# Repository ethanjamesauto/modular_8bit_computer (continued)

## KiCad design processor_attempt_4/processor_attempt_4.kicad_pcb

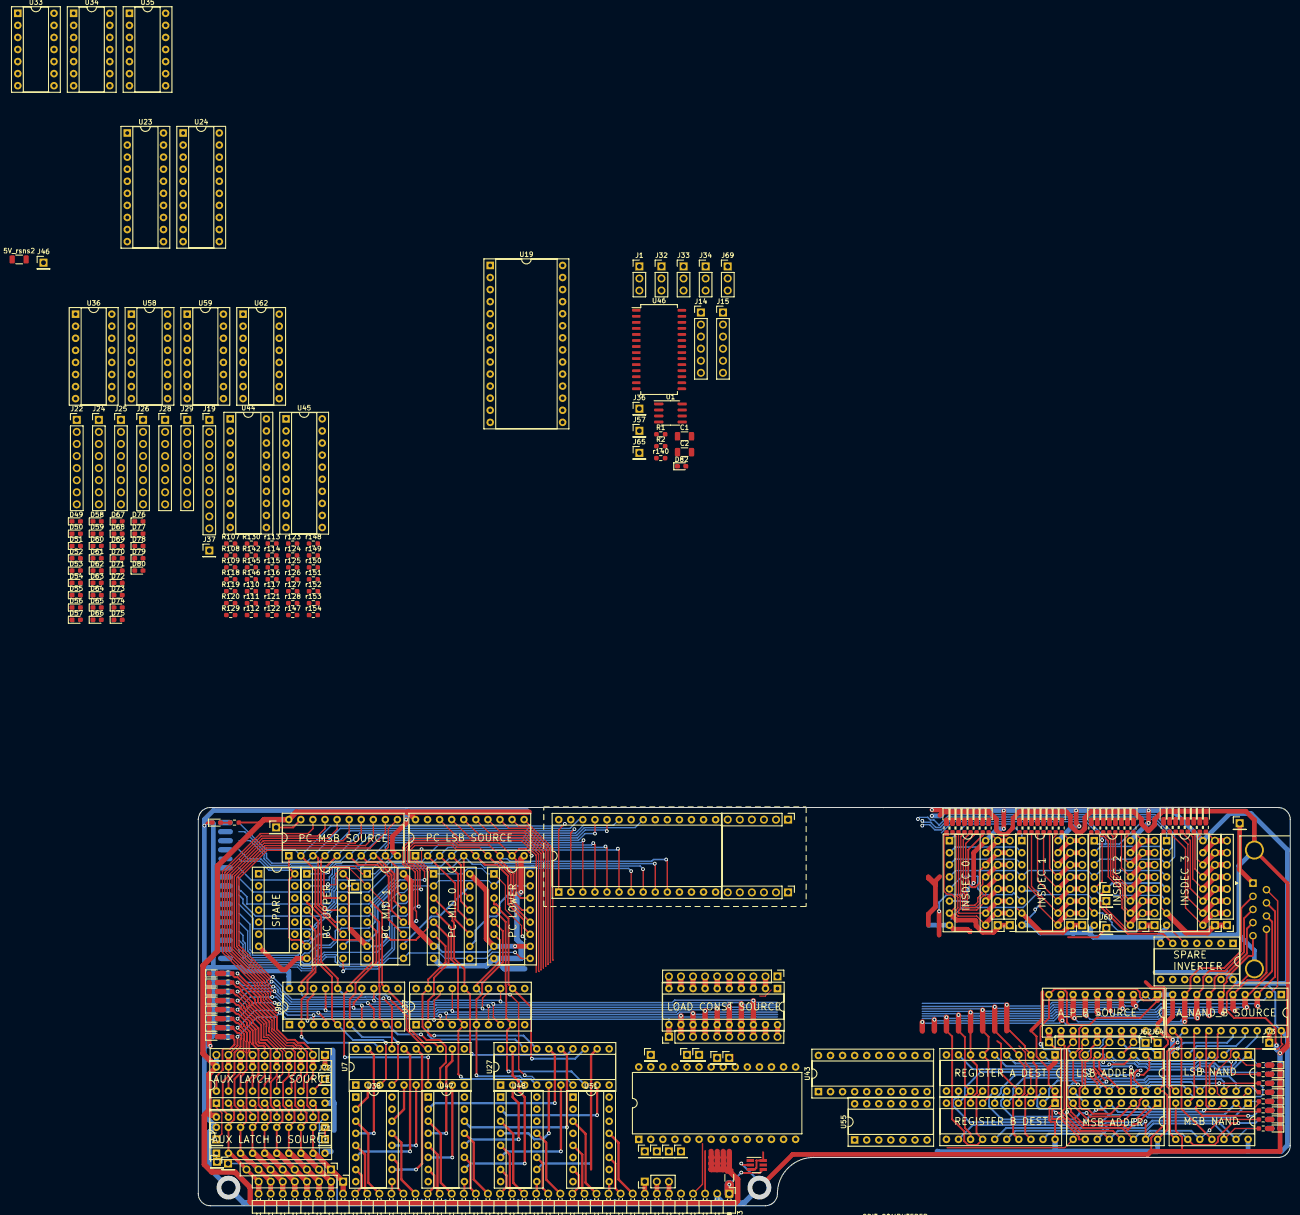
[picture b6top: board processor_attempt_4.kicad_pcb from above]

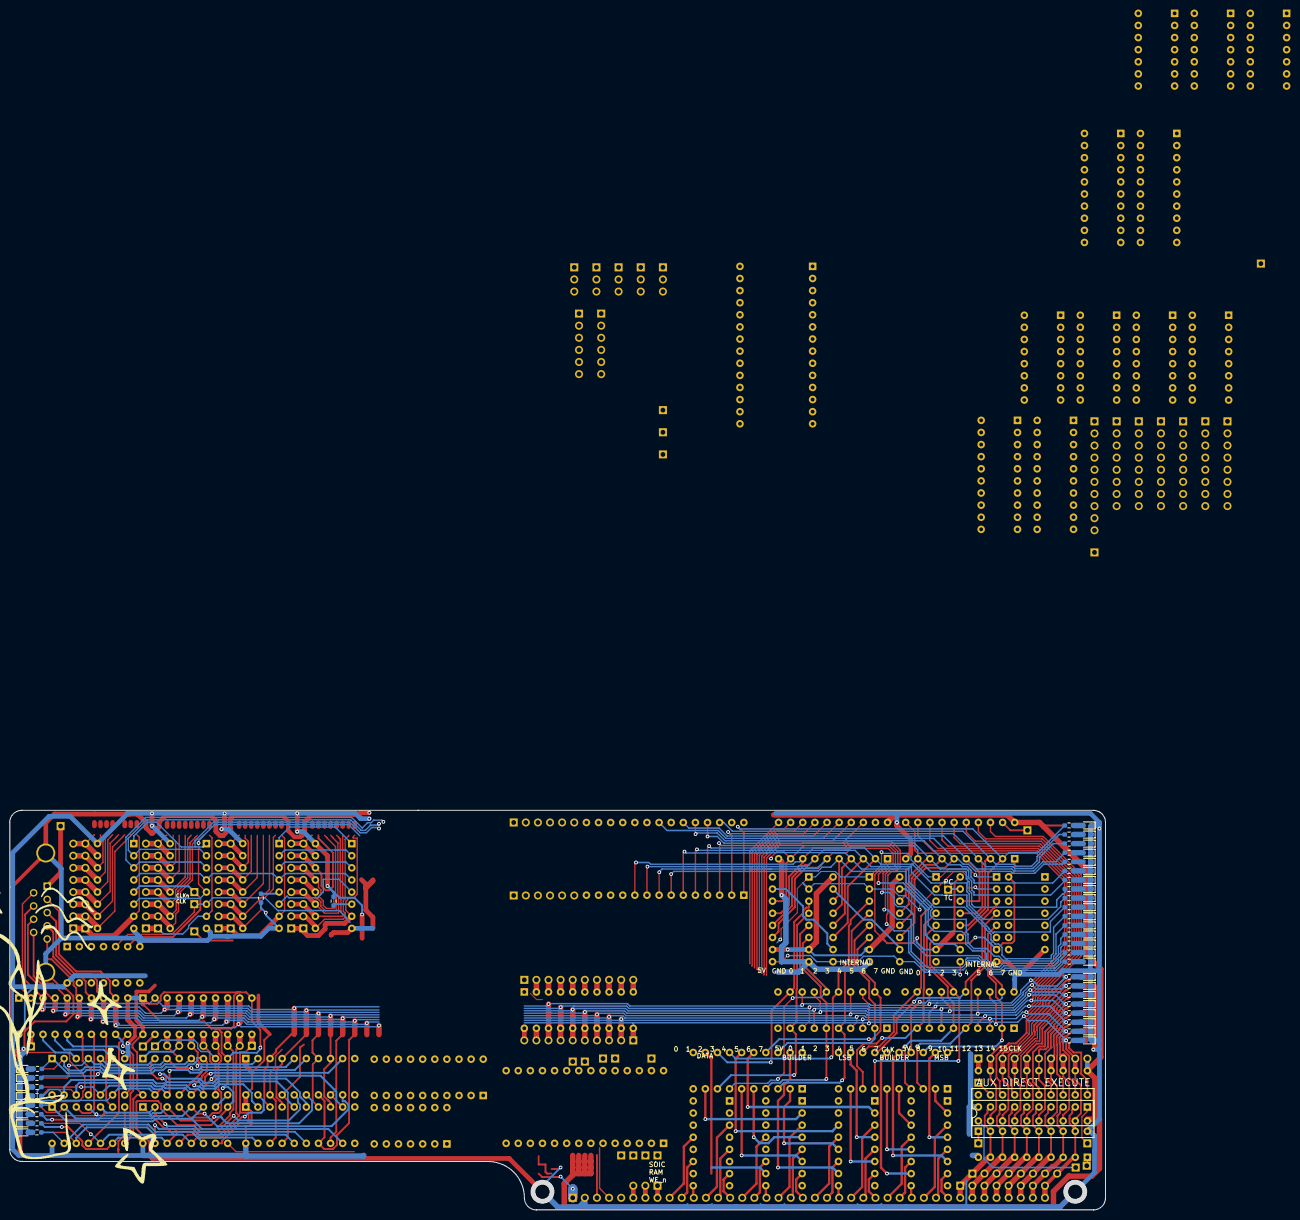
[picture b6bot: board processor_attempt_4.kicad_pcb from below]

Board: 2 copper layers, 229.9 x 83.8 mm, 351 parts (67 on the bottom side), 389 nets.

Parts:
5V_rsns1: 1; R_1206_3216Metric
5V_rsns2: 10k; R_1206_3216Metric
C1, C2: C; C_1206_3216Metric
D1, D17, D25, D33, D41, D49, D49#2, D50, D50#2, D51, D51#2, D52, D52#2, D53, D53#2, D54, D54#2, D55, D55#2, D56, D56#2, D57, D57#2, D58, D58#2, D59, D59#2, D60, D60#2, D61, D61#2, D62, D62#2, D63, D63#2, D64, D64#2, D65, D65#2, D66, D66#2, D67, D67#2, D68, D68#2, D69, D69#2, D70, D70#2, D71, D71#2, D72, D72#2, D73, D73#2, D74, D74#2, D75, D75#2, D76, D76#2, D77, D77#2, D78, D78#2, D79, D79#2, D80, D80#2: A0; LED_0603_1608Metric_Pad1.05x0.95mm_HandSolder
D2, D18, D26, D34, D42: A1; LED_0603_1608Metric_Pad1.05x0.95mm_HandSolder
D3, D19, D27, D35, D43: A2; LED_0603_1608Metric_Pad1.05x0.95mm_HandSolder
D4, D20, D28, D36, D44: A3; LED_0603_1608Metric_Pad1.05x0.95mm_HandSolder
D5, D21, D29, D37, D45, D82: A4; LED_0603_1608Metric_Pad1.05x0.95mm_HandSolder
D6, D22, D30, D38, D46: A5; LED_0603_1608Metric_Pad1.05x0.95mm_HandSolder
D7, D23, D31, D39, D47: A6; LED_0603_1608Metric_Pad1.05x0.95mm_HandSolder
D8, D24, D32, D40, D48: A7; LED_0603_1608Metric_Pad1.05x0.95mm_HandSolder
D9: A8; LED_0603_1608Metric_Pad1.05x0.95mm_HandSolder
D10: A9; LED_0603_1608Metric_Pad1.05x0.95mm_HandSolder
D11: A10; LED_0603_1608Metric_Pad1.05x0.95mm_HandSolder
D12: A11; LED_0603_1608Metric_Pad1.05x0.95mm_HandSolder
D13: A12; LED_0603_1608Metric_Pad1.05x0.95mm_HandSolder
D14: A13; LED_0603_1608Metric_Pad1.05x0.95mm_HandSolder
D15: A14; LED_0603_1608Metric_Pad1.05x0.95mm_HandSolder
D16: A15; LED_0603_1608Metric_Pad1.05x0.95mm_HandSolder
D81: 5V_RAW; LED_0603_1608Metric_Pad1.05x0.95mm_HandSolder
J1, J31, J32, J33, J34, J69: Conn_01x03_Pin; PinHeader_1x03_P2.54mm_Vertical
J3: Conn_01x40_Pin; PinHeader_1x40_P2.54mm_Horizontal
J4, J4#2, J20, J22, J22#2, J23, J24, J24#2, J25, J25#2, J26, J26#2, J27, J28, J28#2, J29, J29#2: Conn_01x08_Pin; PinHeader_1x08_P2.54mm_Vertical
J8, J18, J19, J19#2: Conn_01x10_Pin; PinHeader_1x10_P2.54mm_Vertical
J14, J15, J16, J17: Conn_01x06_Pin; PinHeader_1x06_P2.54mm_Vertical
J21: DB9_Female_MountingHoles; DSUB-9_Female_Horizontal_P2.77x2.84mm_EdgePinOffset4.94mm_H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
J30, J35, J40, J42: Conn_01x01_Pin; PinHeader_1x01_P2.54mm_Vertical
J36, J37, J41, J43, J44, J46, J47, J48, J49, J50, J51, J52, J57, J60, J62, J64, J65, J67, J70, J71, J72, J73, J74: J; PinHeader_1x01_P2.54mm_Vertical
J39: Clock_Aux_Latch_0; PinHeader_1x01_P2.54mm_Vertical
R1, R2, R142#2: R; R_0603_1608Metric_Pad0.98x0.95mm_HandSolder
R107, R108, R109, R118, R119, R120, R129, R130, R141, R142, R145, R146: 0; R_0603_1608Metric_Pad0.98x0.95mm_HandSolder
U1: NE555D; SOIC-8_3.9x4.9mm_P1.27mm
U2, U3, U4, U5: 74LS161; DIP-16_W7.62mm_Socket
U6, U7, U24, U27, U37, U40, U41, U44, U45: 74LS273; DIP-20_W7.62mm_Socket
U18, U19: 28C256; DIP-28_W15.24mm_Socket
U21, U23, U29, U30, U31, U49, U50: 74LS245; DIP-20_W7.62mm_Socket
U25, U26: 74LS574; DIP-20_W7.62mm_Socket
U28: HM62256BLP; DIP-28_W15.24mm
U32, U39: 74LS283; DIP-16_W7.62mm_Socket
U33, U34: 74LS32; DIP-14_W7.62mm_Socket
U35, U55: 74LS30; DIP-14_W7.62mm_Socket
U36, U57, U58, U58#2, U59, U59#2, U60: 74LS138; DIP-16_W7.62mm_Socket
U38, U47, U48, U51: 74LS367; DIP-16_W7.62mm_Socket
U42, U56: 74LS04; DIP-14_W7.62mm_Socket
U43: 74HC688; DIP-20_W7.62mm_Socket
U46: HM62256BLP; SOIC-28W_7.5x18.7mm_P1.27mm
U52, U53: 74LS00; DIP-14_W7.62mm_Socket
U61: 74LVC1G08; SOT-23-6_Handsoldering
U62: DIP-16_W7.62mm_Socket
r51, r52, r53, r54, r55, r56, r57, r58, r59, r60, r61, r62, r63, r64, r65, r66, r67, r68, r69, r70, r71, r72, r73, r74, r75, r76, r77, r78, r79, r80, r81, r82, r83, r84, r85, r86, r87, r88, r89, r90, r91, r92, r93, r94, r95, r96, r97, r98, r107, r108, r109, r110, r110#2, r111, r111#2, r112, r112#2, r113, r113#2, r114, r114#2, r115, r115#2, r116, r116#2, r117, r117#2, r118, r119, r120, r121, r121#2, r122, r122#2, r123, r123#2, r124, r124#2, r125, r125#2, r126, r126#2, r127, r127#2, r128, r128#2, r129, r130, r131, r132, r133, r134, r135, r136, r137, r138, r139, r140, r147, r148, r149, r150, r151, r152, r153, r154: 470; R_0603_1608Metric_Pad0.98x0.95mm_HandSolder

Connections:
+5V: 5V_rsns1.2, 5V_rsns2.2, J3.1, J8.10, J18.1, J19.10, J19#2.10, R1.1, R118.1, R141.1, U1.4 (R), U1.8 (VCC), U2.7 (CEP), U2.10 (CET), U2.16 (VCC), U3.7 (CEP), U3.16 (VCC), U4.7 (CEP), U4.16 (VCC), U5.7 (CEP), U5.16 (VCC), U6.20 (VCC), U7.20 (VCC), U18.27 (~WE), U18.28 (VCC), U19.27 (~WE), U19.28 (VCC), U21.20 (VCC), U23.1 (A->B), U23.20 (VCC), U24.20 (VCC), U25.20 (VCC), U26.20 (VCC), U27.20 (VCC), U28.28 (VCC), U29.1 (A->B), U29.20 (VCC), U30.1 (A->B), U30.20 (VCC), U31.1 (A->B), U31.20 (VCC), U32.16 (VCC), U33.14 (VCC), U34.14 (VCC), U35.14 (VCC), U36.16 (VCC), U37.20 (VCC), U38.16 (VCC), U39.16 (VCC), U40.1 (~Mr), U40.20 (VCC), U41.1 (~Mr), U41.20 (VCC), U42.14 (VCC), U43.20 (VCC), U44.1 (~Mr), U44.20 (VCC), U45.1 (~Mr), U45.20 (VCC), U46.28 (VCC), U47.16 (VCC), U48.16 (VCC), U49.20 (VCC), U50.20 (VCC), U51.16 (VCC), U52.14 (VCC), U53.14 (VCC), U55.14 (VCC), U56.14 (VCC), U57.16 (VCC), U58.16 (VCC), U58#2.16 (VCC), U59.16 (VCC), U59#2.16 (VCC), U60.16 (VCC), U61.5 (VCC), r139.2
/5V_raw: 5V_rsns1.1, U61.4
/APB_0: J20.8, U32.4 (S1), U49.18 (B0)
/APB_1: J20.7, U32.1 (S2), U49.17 (B1)
/APB_2: J20.6, U32.13 (S3), U49.16 (B2)
/APB_3: J20.5, U32.10 (S4), U49.15 (B3)
/APB_4: J20.4, U39.4 (S1), U49.14 (B4)
/APB_5: J20.3, U39.1 (S2), U49.13 (B5)
/APB_6: J20.2, U39.13 (S3), U49.12 (B6)
/APB_7: J20.1, U39.10 (S4), U49.11 (B7)
/A_nand_B_0: U50.18 (B0), U52.3
/A_nand_B_1: U50.17 (B1), U52.6
/A_nand_B_2: U50.16 (B2), U52.8
/A_nand_B_3: U50.15 (B3), U52.11
/A_nand_B_4: U50.14 (B4), U53.3
/A_nand_B_5: U50.13 (B5), U53.6
/A_nand_B_6: U50.12 (B6), U53.8
/A_nand_B_7: U50.11 (B7), U53.11
/Aux_Bus_0_LSB: J3.33, J4.1, U21.2 (A0), U25.9 (D7), U26.9 (D7)
/Aux_Bus_1: J3.34, J4.2, U21.3 (A1), U25.8 (D6), U26.8 (D6)
/Aux_Bus_2: J3.35, J4.3, U21.4 (A2), U25.7 (D5), U26.7 (D5)
/Aux_Bus_3: J3.36, J4.4, U21.5 (A3), U25.6 (D4), U26.6 (D4)
/Aux_Bus_4: J3.37, J4.5, U21.6 (A4), U25.5 (D3), U26.5 (D3)
/Aux_Bus_5: J3.38, J4.6, U21.7 (A5), U25.4 (D2), U26.4 (D2)
/Aux_Bus_6: J3.39, J4.7, J4#2.7, U21.8 (A6), U25.3 (D1), U26.3 (D1)
/Aux_Bus_7_MSB: J3.40, J4.8, U21.9 (A7), U25.2 (D0), U26.2 (D0)
/CLOCK_to_pc: J1.2, J32.1, J32.2, J32.3, J33.1, J33.2, J33.3, J34.1, J34.2, J34.3, J67.1, U2.2 (CP), U3.2 (CP), U4.2 (CP), U5.2 (CP), U42.5, U59.6 (E3), r140.2
/CLOCK_to_pc_n: J70.1, U42.6, U60.5 (E2)
/Data_Bus_0_LSB: J3.9, U51.13 (O6b)
/Data_Bus_1: J3.10, U51.11 (O5b)
/Data_Bus_2: J3.11, U51.9 (O4a)
/Data_Bus_3: J3.12, U51.3 (O1a)
/Data_Bus_4: J3.13, U51.5 (O2a)
/Data_Bus_5: J3.14, U51.7 (O3a)
/Data_Bus_6: J3.15, U48.13 (O6b)
/Data_Bus_7_MSB: J3.16, U48.11 (O5b)
/INTERNAL_BUS_0: J8.2, J19.8, J21.6, U6.13 (D4), U25.12 (Q7), U26.12 (Q7), U28.11 (Q0), U29.11 (B7), U30.11 (B7), U31.18 (B0), U37.13 (D4), U40.3 (D0), U41.3 (D0), U44.3 (D0), U45.3 (D0), U46.11 (Q0), U49.2 (A0), U50.2 (A0), r67.2
/INTERNAL_BUS_1: J8.3, J19.7, J21.7, U6.8 (D3), U25.13 (Q6), U26.13 (Q6), U28.12 (Q1), U29.12 (B6), U30.12 (B6), U31.17 (B1), U37.8 (D3), U40.4 (D1), U41.4 (D1), U44.4 (D1), U45.4 (D1), U46.12 (Q1), U49.3 (A1), U50.3 (A1), r68.2
/INTERNAL_BUS_2: J8.4, J19.6, J21.8, U6.7 (D2), U25.14 (Q5), U26.14 (Q5), U28.13 (Q2), U29.13 (B5), U30.13 (B5), U31.16 (B2), U37.7 (D2), U40.7 (D2), U41.7 (D2), U44.7 (D2), U45.7 (D2), U46.13 (Q2), U49.4 (A2), U50.4 (A2), r69.2
/INTERNAL_BUS_3: J8.5, J19.5, J21.9, U6.14 (D5), U25.15 (Q4), U26.15 (Q4), U28.15 (Q3), U29.14 (B4), U30.14 (B4), U31.15 (B3), U37.14 (D5), U40.8 (D3), U41.8 (D3), U44.8 (D3), U45.8 (D3), U46.15 (Q3), U49.5 (A3), U50.5 (A3), r70.2
/INTERNAL_BUS_4: J8.6, J19.4, J21.5, U6.17 (D6), U25.16 (Q3), U26.16 (Q3), U28.16 (Q4), U29.15 (B3), U30.15 (B3), U31.14 (B4), U37.17 (D6), U40.13 (D4), U41.13 (D4), U44.13 (D4), U45.13 (D4), U46.16 (Q4), U49.6 (A4), U50.6 (A4), r71.2
/INTERNAL_BUS_5: J8.7, J19.3, J21.4, U6.4 (D1), U25.17 (Q2), U26.17 (Q2), U28.17 (Q5), U29.16 (B2), U30.16 (B2), U31.13 (B5), U37.4 (D1), U40.14 (D5), U41.14 (D5), U44.14 (D5), U45.14 (D5), U46.17 (Q5), U49.7 (A5), U50.7 (A5), r72.2
/INTERNAL_BUS_6: J8.8, J19.2, J21.3, U6.3 (D0), U25.18 (Q1), U26.18 (Q1), U28.18 (Q6), U29.17 (B1), U30.17 (B1), U31.12 (B6), U37.3 (D0), U40.17 (D6), U41.17 (D6), U44.17 (D6), U45.17 (D6), U46.18 (Q6), U49.8 (A6), U50.8 (A6), r73.2
/INTERNAL_BUS_7: J8.9, J19.1, J21.2, U6.18 (D7), U25.19 (Q0), U26.19 (Q0), U28.19 (Q7), U29.18 (B0), U30.18 (B0), U31.11 (B7), U37.18 (D7), U40.18 (D7), U41.18 (D7), U44.18 (D7), U45.18 (D7), U46.19 (Q7), U49.9 (A7), U50.9 (A7), r74.2
/Load_Constant_OE_n: J19.9, J19#2.9, U31.19 (CE)
/PC_0: J69.1, J69.2, J69.3, U2.14 (Q0), U30.9 (A7), r51.2
/PC_1: U2.13 (Q1), U18.10 (A0), U19.10 (A0), U30.8 (A6), r52.2
/PC_2: U2.12 (Q2), U18.9 (A1), U19.9 (A1), U30.7 (A5), r53.2
/PC_3: U2.11 (Q3), U18.8 (A2), U19.8 (A2), U30.6 (A4), r54.2
/PC_4: U3.14 (Q0), U18.7 (A3), U19.7 (A3), U30.5 (A3), r55.2
/PC_5: U3.13 (Q1), U18.6 (A4), U19.6 (A4), U30.4 (A2), r56.2
/PC_6: U3.12 (Q2), U18.5 (A5), U19.5 (A5), U30.3 (A1), r57.2
/PC_7: U3.11 (Q3), U18.4 (A6), U19.4 (A6), U30.2 (A0), r58.2
/PC_8: U4.14 (Q0), U18.3 (A7), U19.3 (A7), U29.9 (A7), r59.2
/PC_9: U4.13 (Q1), U18.25 (A8), U19.25 (A8), U29.8 (A6), r60.2
/PC_10: U4.12 (Q2), U18.24 (A9), U19.24 (A9), U29.7 (A5), r61.2
/PC_11: U4.11 (Q3), U18.21 (A10), U19.21 (A10), U29.6 (A4), r62.2
/PC_12: U5.14 (Q0), U18.23 (A11), U19.23 (A11), U29.5 (A3), r63.2
/PC_13: U5.13 (Q1), U18.2 (A12), U19.2 (A12), U29.4 (A2), r64.2
/PC_14: U5.12 (Q2), U18.26 (A13), U19.26 (A13), U29.3 (A1), r65.2
/PC_15: U5.11 (Q3), U18.1 (A14), U19.1 (A14), U29.2 (A0), r66.2
/PC_load_n: U2.9 (~PE), U3.9 (~PE), U4.9 (~PE), U5.9 (~PE)
/RA_0: U32.5 (A1), U40.2 (Q0), U43.12 (R4), U52.2, r83.2
/RA_1: U32.3 (A2), U40.5 (Q1), U43.14 (R5), U52.4, r84.2
/RA_2: U32.14 (A3), U40.6 (Q2), U43.16 (R6), U52.10, r85.2
/RA_3: U32.12 (A4), U40.9 (Q3), U43.18 (R7), U52.12, r86.2
/RA_4: U39.5 (A1), U40.12 (Q4), U43.3 (R0), U53.2, r87.2
/RA_5: U39.3 (A2), U40.15 (Q5), U43.5 (R1), U53.4, r88.2
/RA_6: U39.14 (A3), U40.16 (Q6), U43.7 (R2), U53.10, r89.2
/RA_7: U39.12 (A4), U40.19 (Q7), U43.9 (R3), U53.12, r90.2
/RB_0: U32.6 (B1), U41.2 (Q0), U43.11 (P4), U52.1, U55.2, r91.2
/RB_1: U32.2 (B2), U41.5 (Q1), U43.13 (P5), U52.5, U55.1, r92.2
/RB_2: U32.15 (B3), U41.6 (Q2), U43.15 (P6), U52.9, U55.12, r93.2
/RB_3: U32.11 (B4), U41.9 (Q3), U43.17 (P7), U52.13, U55.11, r94.2
/RB_4: U39.6 (B1), U41.12 (Q4), U43.2 (P0), U53.1, U55.6, r95.2
/RB_5: U39.2 (B2), U41.15 (Q5), U43.4 (P1), U53.5, U55.5, r96.2
/RB_6: U39.15 (B3), U41.16 (Q6), U43.6 (P2), U53.9, U55.4, r97.2
/RB_7: U39.11 (B4), U41.19 (Q7), U43.8 (P3), U53.13, U55.3, r98.2
/a_equals_b: J37.1, U43.19 (P=R)
/a_plus_b_carry_out: U33.9, U39.9 (C4)
/addr_bus_0: J3.17, U48.9 (O4a)
/addr_bus_1: J3.18, U48.3 (O1a)
/addr_bus_2: J3.19, U48.5 (O2a)
/addr_bus_3: J3.20, U48.7 (O3a)
/addr_bus_4: J3.21, U47.13 (O6b)
/addr_bus_5: J3.22, U47.11 (O5b)
/addr_bus_6: J3.23, U47.9 (O4a)
/addr_bus_7: J3.24, U47.3 (O1a)
/addr_bus_8: J3.25, U47.5 (O2a)
/addr_bus_9: J3.26, U47.7 (O3a)
/addr_bus_10: J3.27, U38.13 (O6b)
/addr_bus_11: J3.28, U38.11 (O5b)
/addr_bus_12: J3.29, U38.9 (O4a)
/addr_bus_13: J3.30, U38.3 (O1a)
/addr_bus_14: J3.31, U38.5 (O2a)
/addr_bus_15: J3.32, U38.7 (O3a)
/addr_pre_buf_0: U27.12 (Q4), U48.10 (I4)
/addr_pre_buf_1: U27.9 (Q3), U48.2 (I1)
/addr_pre_buf_2: U27.5 (Q1), U48.4 (I2)
/addr_pre_buf_3: U27.6 (Q2), U48.6 (I3)
/addr_pre_buf_4: U27.15 (Q5), U47.14 (I6)
/addr_pre_buf_5: U27.2 (Q0), U47.12 (I5)
/addr_pre_buf_6: U27.19 (Q7), U47.10 (I4)
/addr_pre_buf_7: U27.16 (Q6), U47.2 (I1)
/addr_pre_buf_8: U7.12 (Q4), U47.4 (I2)
/addr_pre_buf_9: U7.9 (Q3), U47.6 (I3)
/addr_pre_buf_10: U7.5 (Q1), U38.14 (I6)
/addr_pre_buf_11: U7.6 (Q2), U38.12 (I5)
/addr_pre_buf_12: U7.15 (Q5), U38.10 (I4)
/addr_pre_buf_13: U7.2 (Q0), U38.2 (I1)
/addr_pre_buf_14: U7.19 (Q7), U38.4 (I2)
/addr_pre_buf_15: U7.16 (Q6), U38.6 (I3)
/b_equals_f_f: J57.1, U55.8
/clk: J1.1, J3.3, R108.1
/clock_build_constant: J22#2.1, J24#2.1, U36.7 (O7), r117#2.2
/clock_builder_lower: J22#2.8, J24#2.8, U36.15 (O0), r110.2
/clock_builder_upper: J22#2.7, J24#2.7, U36.14 (O1), r111.2
/clock_register_a: J22#2.5, J24#2.5, U36.12 (O3), r113.2
/clock_register_b: J22#2.4, J24#2.4, U36.11 (O4), r114.2
/cond_0: U33.3, U35.1
/cond_1: U33.6, U35.2
/cond_2: U33.8, U35.3
/cond_3: U33.11, U35.4
/cond_4: U34.3, U35.5
/cond_5: U34.6, U35.6
/cond_6: U34.8, U35.11
/cond_7: U34.11, U35.12
/ctrl_8: J22.8, J24.8, U58#2.15 (O0), r130.2
/ctrl_9: J22.7, J24.7, U58#2.14 (O1), r129.2
/ctrl_10: J22.6, J24.6, U58#2.13 (O2), r128.2
/ctrl_11: J22.5, J24.5, U58#2.12 (O3), r127.2
/ctrl_12: J22.4, J24.4, U58#2.11 (O4), r126.2
/ctrl_13: J22.3, J24.3, U58#2.10 (O5), r125#2.2
/ctrl_14: J22.2, J24.2, U58#2.9 (O6), r124#2.2
/ctrl_15: J22.1, J24.1, U58#2.7 (O7), r123.2
/ctrl_16: J26.8, J28#2.8, U59.15 (O0), r107.2
/ctrl_17: J26.7, J28#2.7, U59.14 (O1), r108.2
/ctrl_18: J26.6, J28#2.6, U59.13 (O2), r109.2
/ctrl_19: J26.5, J28#2.5, U59.12 (O3), r110#2.2
/ctrl_20: J26.4, J28#2.4, U59.11 (O4), r111#2.2
/ctrl_21: J26.3, J28#2.3, U59.10 (O5), r112#2.2
/ctrl_22: J26.2, J28#2.2, U59.9 (O6), r113#2.2
/ctrl_23: J26.1, J28#2.1, U59.7 (O7), r114#2.2
/ctrl_24: J25.8, J29.8, U60.15 (O0), r115.2
/ctrl_25: J25.7, J29.7, U60.14 (O1), r116#2.2
/ctrl_26: J25.6, J29.6, U60.13 (O2), r117.2
/ctrl_27: J25.5, J29.5, U60.12 (O3), r118.2
/ctrl_28: J25.4, J29.4, U60.11 (O4), r119.2
/ctrl_29: J25.3, J29.3, U60.10 (O5), r120.2
/ctrl_30: J25.2, J29.2, U60.9 (O6), r121.2
/ctrl_31: J25.1, J29.1, U60.7 (O7), r122.2
/external_write_enable_n: J22#2.2, J24#2.2, U36.9 (O6), r116.2
/extra_control_one: J23.3, J27.3, U34.5, U57.10 (O5), r133.2
/extra_control_three: J23.1, J27.1, U34.13, U57.7 (O7), r131.2
/extra_control_two: J23.2, J27.2, U34.10, U57.9 (O6), r132.2
/extra_control_zero: J23.4, J27.4, U7.11 (Cp), U27.11 (Cp), U34.2, U57.11 (O4), r134.2
/extra_dest_clock: J22#2.3, J24#2.3, U36.10 (O5), r115#2.2
/flag_0: J28.8, J29#2.8, U59#2.15 (O0), r147.2
/flag_1: J28.7, J29#2.7, U59#2.14 (O1), r148.2
/flag_2: J28.6, J29#2.6, U59#2.13 (O2), r149.2
/flag_3: J28.5, J29#2.5, U59#2.12 (O3), r150.2
/flag_4: J28.4, J29#2.4, U59#2.11 (O4), r151.2
/flag_5: J28.3, J29#2.3, U59#2.10 (O5), r152.2
/flag_6: J28.2, J29#2.2, U59#2.9 (O6), r153.2
/flag_7: J28.1, J29#2.1, U59#2.7 (O7), r154.2
/instruction_0: U18.11 (D0), U19.11 (D0), U21.18 (B0), U23.2 (A0), U24.3 (D0), r75.2
/instruction_1: U18.12 (D1), U19.12 (D1), U21.17 (B1), U23.3 (A1), U24.4 (D1), r76.2
/instruction_2: U18.13 (D2), U19.13 (D2), U21.16 (B2), U23.4 (A2), U24.7 (D2), r77.2
/instruction_3: R119.1, R145.1, U18.15 (D3), U19.15 (D3), U21.15 (B3), U23.5 (A3), U24.8 (D3), r78.2
/instruction_4: U18.16 (D4), U19.16 (D4), U21.14 (B4), U23.6 (A4), U24.13 (D4), r79.2
/instruction_5: U18.17 (D5), U19.17 (D5), U21.13 (B5), U23.7 (A5), U24.14 (D5), r80.2
/instruction_6: U18.18 (D6), U19.18 (D6), U21.12 (B6), U23.8 (A6), U24.17 (D6), r81.2
/instruction_7: R107.1, R120.1, R146.1, U18.19 (D7), U19.19 (D7), U21.11 (B7), U23.9 (A7), U24.18 (D7), r82.2
/instruction_valid_n: U58#2.4 (E1), U59.4 (E1), U60.4 (E1)
/jump_cond_a_equals_b: J23.8, J27.8, U33.2, U57.15 (O0), r138.2
/jump_cond_a_plus_b_carry_out: J23.6, J27.6, U33.10, U57.13 (O2), r136.2
/jump_cond_b_equals_f_f: J23.7, J27.7, U33.5, U57.14 (O1), r137.2
/jump_cond_b_negative: J23.5, J27.5, U33.13, U57.12 (O3), r135.2
/mar_0: U28.10 (A0), U45.2 (Q0), U46.10 (A0)
/mar_1: U28.9 (A1), U45.5 (Q1), U46.9 (A1)
/mar_2: U28.8 (A2), U45.6 (Q2), U46.8 (A2)
/mar_3: U28.7 (A3), U45.9 (Q3), U46.7 (A3)
/mar_4: U28.6 (A4), U45.12 (Q4), U46.6 (A4)
/mar_5: U28.5 (A5), U45.15 (Q5), U46.5 (A5)
/mar_6: U28.4 (A6), U45.16 (Q6), U46.4 (A6)
/mar_7: U28.3 (A7), U45.19 (Q7), U46.3 (A7)
/mar_8: U28.25 (A8), U44.2 (Q0), U46.25 (A8)
/mar_9: U28.24 (A9), U44.5 (Q1), U46.24 (A9)
/mar_10: U28.21 (A10), U44.6 (Q2), U46.21 (A10)
/mar_11: U28.23 (A11), U44.9 (Q3), U46.23 (A11)
/mar_12: U28.2 (A12), U44.12 (Q4), U46.2 (A12)
/mar_13: U28.26 (A13), U44.15 (Q5)
/mar_14: U28.1 (A14), U44.16 (Q6)
/pc_reset_n: 5V_rsns2.1, J3.4, U2.1 (~MR), U3.1 (~MR), U4.1 (~MR), U5.1 (~MR), U7.1 (~Mr), U24.1 (~Mr), U27.1 (~Mr)
/ram_write_enable_n: J22#2.6, J24#2.6, U36.13 (O2), r112.2
/source_0: J25#2.8, J26#2.8, U58.15 (O0), r121#2.2
/source_1: J25#2.7, J26#2.7, U58.14 (O1), r122#2.2
/source_2: J25#2.6, J26#2.6, U58.13 (O2), r123#2.2
/source_3: J25#2.5, J26#2.5, U58.12 (O3), r124.2
/source_4: J25#2.4, J26#2.4, U58.11 (O4), r125.2
/source_5: J25#2.3, J26#2.3, U58.10 (O5), r126#2.2
/source_6: J25#2.2, J26#2.2, U58.9 (O6), r127#2.2
/source_7: J25#2.1, J26#2.1, U58.7 (O7), r128#2.2
/to_PC_0: U2.3 (D0), U27.13 (D4), U37.12 (Q4)
/to_PC_1: U2.4 (D1), U27.8 (D3), U37.9 (Q3)
/to_PC_2: U2.5 (D2), U27.4 (D1), U37.6 (Q2)
/to_PC_3: U2.6 (D3), U27.7 (D2), U37.15 (Q5)
/to_PC_4: U3.3 (D0), U27.14 (D5), U37.16 (Q6)
/to_PC_5: U3.4 (D1), U27.3 (D0), U37.5 (Q1)
/to_PC_6: U3.5 (D2), U27.18 (D7), U37.2 (Q0)
/to_PC_7: U3.6 (D3), U27.17 (D6), U37.19 (Q7)
/to_PC_8: U4.3 (D0), U6.12 (Q4), U7.13 (D4)
/to_PC_9: U4.4 (D1), U6.9 (Q3), U7.8 (D3)
/to_PC_10: U4.5 (D2), U6.6 (Q2), U7.4 (D1)
/to_PC_11: U4.6 (D3), U6.15 (Q5), U7.7 (D2)
/to_PC_12: U5.3 (D0), U6.16 (Q6), U7.14 (D5)
/to_PC_13: U5.4 (D1), U6.5 (Q1), U7.3 (D0)
/to_PC_14: U5.5 (D2), U6.2 (Q0), U7.18 (D7)
/to_PC_15: U5.6 (D3), U6.19 (Q7), U7.17 (D6)
/to_insdec_0: U23.18 (B0), U58.1 (A0), U59#2.1 (A0)
/to_insdec_1: U23.17 (B1), U58.2 (A1), U59#2.2 (A1)
/to_insdec_2: U23.16 (B2), U58.3 (A2), U59#2.3 (A2)
/to_insdec_4: U23.14 (B4), U36.1 (A0), U57.1 (A0), U58#2.1 (A0)
/to_insdec_5: U23.13 (B5), U36.2 (A1), U57.2 (A1), U58#2.2 (A1)
/to_insdec_6: U23.12 (B6), U36.3 (A2), U57.3 (A2), U58#2.3 (A2)
/to_insdec_7: U23.11 (B7), U58#2.6 (E3)
/to_insdec_8: U24.2 (Q0), U59.1 (A0), U60.1 (A0)
/to_insdec_9: U24.5 (Q1), U59.2 (A1), U60.2 (A1)
/to_insdec_10: U24.6 (Q2), U59.3 (A2), U60.3 (A2)
/to_insdec_11: U24.9 (Q3), U59.5 (E2), U60.6 (E3)
GND: C1.2, C2.2, D1.1 (K), D2.1 (K), D3.1 (K), D4.1 (K), D5.1 (K), D6.1 (K), D7.1 (K), D8.1 (K), D9.1 (K), D10.1 (K), D11.1 (K), D12.1 (K), D13.1 (K), D14.1 (K), D15.1 (K), D16.1 (K), D17.1 (K), D18.1 (K), D19.1 (K), D20.1 (K), D21.1 (K), D22.1 (K), D23.1 (K), D24.1 (K), D25.1 (K), D26.1 (K), D27.1 (K), D28.1 (K), D29.1 (K), D30.1 (K), D31.1 (K), D32.1 (K), D33.1 (K), D34.1 (K), D35.1 (K), D36.1 (K), D37.1 (K), D38.1 (K), D39.1 (K), D40.1 (K), D41.1 (K), D42.1 (K), D43.1 (K), D44.1 (K), D45.1 (K), D46.1 (K), D47.1 (K), D48.1 (K), D49.1 (K), D49#2.2 (A), D50.2 (A), D50#2.1 (K), D51.1 (K), D51#2.2 (A), D52.2 (A), D52#2.1 (K), D53.1 (K), D53#2.2 (A), D54.1 (K), D54#2.2 (A), D55.1 (K), D55#2.2 (A), D56.2 (A), D56#2.1 (K), D57.1 (K), D57#2.2 (A), D58.1 (K), D58#2.2 (A), D59.1 (K), D59#2.2 (A), D60.2 (A), D60#2.1 (K), D61.2 (A), D61#2.1 (K), D62.2 (A), D62#2.1 (K), D63.2 (A), D63#2.1 (K), D64.2 (A), D64#2.1 (K), D65.1 (K), D65#2.2 (A), D66.1 (K), D66#2.2 (A), D67.1 (K), D67#2.2 (A), D68.2 (A), D68#2.1 (K), D69.1 (K), D69#2.2 (A), D70.1 (K), D70#2.2 (A), D71.1 (K), D71#2.2 (A), D72.2 (A), D72#2.1 (K), D73.2 (A), D73#2.1 (K), D74.2 (A), D74#2.1 (K), D75.1 (K), D75#2.2 (A), D76.2 (A), D76#2.1 (K), D77.2 (A), D77#2.1 (K), D78.2 (A), D78#2.1 (K), D79.1 (K), D79#2.2 (A), D80.1 (K), D80#2.2 (A), D81.1 (K), D82.1 (K), J3.2, J18.10, J21.0 (PAD), J60.1, R142#2.1, U1.1 (GND), U2.8 (GND), U3.8 (GND), U4.8 (GND), U5.8 (GND), U6.10 (GND), U7.10 (GND), U18.14 (GND), U18.20 (~CS), U18.22 (~OE), U19.14 (GND), U19.20 (~CS), U19.22 (~OE), U21.10 (GND), U23.10 (GND), U24.10 (GND), U25.10 (GND), U26.10 (GND), U27.10 (GND), U28.14 (GND), U29.10 (GND), U30.10 (GND), U31.10 (GND), U32.8 (GND), U33.7 (GND), U34.7 (GND), U35.7 (GND), U36.8 (GND), U37.10 (GND), U38.8 (GND), U39.8 (GND), U40.10 (GND), U41.10 (GND), U42.7 (GND), U43.1 (G), U43.10 (GND), U44.10 (GND), U45.10 (GND), U46.14 (GND), U47.8 (GND), U48.8 (GND), U49.1 (A->B), U49.10 (GND), U50.1 (A->B), U50.10 (GND), U51.8 (GND), U52.7 (GND), U53.7 (GND), U55.7 (GND), U56.7 (GND), U57.8 (GND), U58.8 (GND), U58#2.8 (GND), U59.8 (GND), U59#2.8 (GND), U60.8 (GND), U61.2, U62.8 (GND)
unnamed: D1.2 (A), r51.1
unnamed: D2.2 (A), r52.1
unnamed: D3.2 (A), r53.1
unnamed: D4.2 (A), r54.1
unnamed: D5.2 (A), r55.1
unnamed: D6.2 (A), r56.1
unnamed: D7.2 (A), r57.1
unnamed: D8.2 (A), r58.1
unnamed: D9.2 (A), r59.1
unnamed: D10.2 (A), r60.1
unnamed: D11.2 (A), r61.1
unnamed: D12.2 (A), r62.1
unnamed: D13.2 (A), r63.1
unnamed: D14.2 (A), r64.1
unnamed: D15.2 (A), r65.1
unnamed: D16.2 (A), r66.1
unnamed: D17.2 (A), r67.1
unnamed: D18.2 (A), r68.1
unnamed: D19.2 (A), r69.1
unnamed: D20.2 (A), r70.1
unnamed: D21.2 (A), r71.1
unnamed: D22.2 (A), r72.1
unnamed: D23.2 (A), r73.1
unnamed: D24.2 (A), r74.1
unnamed: D25.2 (A), r75.1
unnamed: D26.2 (A), r76.1
unnamed: D27.2 (A), r77.1
unnamed: D28.2 (A), r78.1
unnamed: D29.2 (A), r79.1
unnamed: D30.2 (A), r80.1
unnamed: D31.2 (A), r81.1
unnamed: D32.2 (A), r82.1
unnamed: D33.2 (A), r83.1
unnamed: D34.2 (A), r84.1
unnamed: D35.2 (A), r85.1
unnamed: D36.2 (A), r86.1
unnamed: D37.2 (A), r87.1
unnamed: D38.2 (A), r88.1
unnamed: D39.2 (A), r89.1
unnamed: D40.2 (A), r90.1
unnamed: D41.2 (A), r91.1
unnamed: D42.2 (A), r92.1
unnamed: D43.2 (A), r93.1
unnamed: D44.2 (A), r94.1
unnamed: D45.2 (A), r95.1
unnamed: D46.2 (A), r96.1
unnamed: D47.2 (A), r97.1
unnamed: D48.2 (A), r98.1
unnamed: D49.2 (A), r107.1
unnamed: D49#2.1 (K), r110.1
unnamed: D50#2.2 (A), r108.1
unnamed: D50.1 (K), r111.1
unnamed: D51.2 (A), r109.1
unnamed: D51#2.1 (K), r112.1
unnamed: D52#2.2 (A), r110#2.1
unnamed: D52.1 (K), r113.1
unnamed: D53.2 (A), r111#2.1
unnamed: D53#2.1 (K), r114.1
unnamed: D54.2 (A), r112#2.1
unnamed: D54#2.1 (K), r115#2.1
unnamed: D55.2 (A), r113#2.1
unnamed: D55#2.1 (K), r116.1
unnamed: D56#2.2 (A), r114#2.1
unnamed: D56.1 (K), r117#2.1
unnamed: D57.2 (A), r115.1
unnamed: D57#2.1 (K), r121#2.1
unnamed: D58.2 (A), r116#2.1
unnamed: D58#2.1 (K), r122#2.1
unnamed: D59.2 (A), r117.1
unnamed: D59#2.1 (K), r123#2.1
unnamed: D60#2.2 (A), r118.1
unnamed: D60.1 (K), r124.1
unnamed: D61#2.2 (A), r119.1
unnamed: D61.1 (K), r125.1
unnamed: D62#2.2 (A), r120.1
unnamed: D62.1 (K), r126#2.1
unnamed: D63#2.2 (A), r121.1
unnamed: D63.1 (K), r127#2.1
unnamed: D64#2.2 (A), r122.1
unnamed: D64.1 (K), r128#2.1
unnamed: D65.2 (A), r123.1
unnamed: D65#2.1 (K), r147.1
unnamed: D66.2 (A), r124#2.1
unnamed: D66#2.1 (K), r148.1
unnamed: D67.2 (A), r125#2.1
unnamed: D67#2.1 (K), r149.1
unnamed: D68#2.2 (A), r126.1
unnamed: D68.1 (K), r150.1
unnamed: D69.2 (A), r127.1
unnamed: D69#2.1 (K), r151.1
unnamed: D70.2 (A), r128.1
unnamed: D70#2.1 (K), r152.1
unnamed: D71.2 (A), r129.1
unnamed: D71#2.1 (K), r153.1
unnamed: D72#2.2 (A), r130.1
unnamed: D72.1 (K), r154.1
unnamed: D73.1 (K), r131.1
unnamed: D74.1 (K), r132.1
unnamed: D75#2.1 (K), r133.1
unnamed: D76.1 (K), r134.1
unnamed: D77.1 (K), r135.1
unnamed: D78.1 (K), r136.1
unnamed: D79#2.1 (K), r137.1
unnamed: D80#2.1 (K), r138.1
unnamed: D81.2 (A), r139.1
unnamed: D82.2 (A), r140.1
unnamed: J1.3, U1.3 (Q)
unnamed: J3.6, J31.3
unnamed: J3.7, J31.2
unnamed: J3.8, J31.1
unnamed: J8.1, U25.11 (Cp)
unnamed: J18.2, U31.2 (A0)
unnamed: J18.3, U31.3 (A1)
unnamed: J18.4, U31.4 (A2)
unnamed: J18.5, U31.5 (A3)
unnamed: J18.6, U31.6 (A4)
unnamed: J18.7, U31.7 (A5)
unnamed: J18.8, U31.8 (A6)
unnamed: J18.9, U31.9 (A7)
unnamed: J30.1, U26.1 (OE)
unnamed: J35.1, U25.1 (OE)
unnamed: J36.1, U23.19 (CE)
unnamed: J39.1, U26.11 (Cp)
unnamed: J40.1, U29.19 (CE)
unnamed: J42.1, U5.15 (TC)
unnamed: J46.1, U44.11 (Cp)
unnamed: J47.1, U28.20 (~CS)
unnamed: J48.1, U28.22 (~OE)
unnamed: J49.1, U28.27 (~WE)
unnamed: J50.1, U46.20 (~CS)
unnamed: J51.1, U46.22 (~OE)
unnamed: J52.1, U46.27 (~WE)
unnamed: J62.1, U32.7 (C0)
unnamed: J64.1, U49.19 (CE)
unnamed: J65.1, U24.11 (Cp)
unnamed: J71.1, U21.1 (A->B)
unnamed: J72.1, U21.19 (CE)
unnamed: J73.1, U50.19 (CE)
unnamed: J21.1, J74.1
unnamed: C1.1, U1.5 (CV)
unnamed: R1.2, R2.1, U1.7 (DIS)
unnamed: C2.1, R2.2, U1.2 (TR), U1.6 (THR)
unnamed: U2.15 (TC), U3.10 (CET)
unnamed: U3.15 (TC), U4.10 (CET)
unnamed: U4.15 (TC), U5.10 (CET)
unnamed: U32.9 (C4), U39.7 (C0)
unnamed: R109.2, U36.4 (E1)
unnamed: R108.2, U36.5 (E2)
unnamed: R107.2, U36.6 (E3)
unnamed: R146.2, U57.4 (E1)
unnamed: R145.2, U57.5 (E2)
unnamed: R141.2, U57.6 (E3)
unnamed: R120.2, U58.4 (E1)
unnamed: R119.2, R142#2.2, U58.5 (E2), U58#2.5 (E2)
unnamed: R118.2, U58.6 (E3)
unnamed: R142.2, U59#2.4 (E1)
unnamed: R130.2, U59#2.5 (E2)
unnamed: R129.2, U59#2.6 (E3)
